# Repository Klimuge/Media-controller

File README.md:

# MediaController

Компактный портативный медиаконтроллер на ESP32-S3 с механическими кнопками и Bluetooth.

## Что это
Устройство подключается к телефону или компьютеру по Bluetooth или type-c кабелю и управляет медиа:
следующий/предыдущий трек, пауза, громкость, выводит название трека, автора, сколько трека прошло,
сколько осталось или сколько он длится. Что выводится на экране и что делает четвёртая кнопка можно настроить

## Железо
- ESP32-S3-WROOM-1-N16R8
- Cherry MX Red — механические кнопки
- EC11 — энкодер для громкости
- LCD 2004 + I2C — дисплей
- LiPo 3.7В 3000мАч аккумулятор
- TP4056 — зарядка
- AP2112K-3.3 — LDO, питание логики 3.3V
- MTS-123 — тумблер переключения режимов

## Что сделано
- Схема и PCB в KiCad
- BOM с футпринтами
- 3д модели корпуса
- План кода

## Программная часть (не реализована)

Система состоит из трёх компонентов.

### Прошивка ESP32

NimBLE-Arduino (h2zero) — устройство представляется системе как BLE HID-клавиатура
и отправляет медиакейкоды. ESP32-S3 работает как составное USB-устройство одновременно:
HID (медиаклавиатура) + CDC (виртуальный COM-порт для агента).
ArduinoJson парсит входящие JSON-сообщения от агента и обновляет LCD.
Тумблер MTS-123 переключает режимы, состояние читается через GPIO38/GPIO39 с INPUT_PULLDOWN.
Энкодер EC11 управляет громкостью через прерывания.

### Агент

Фоновое приложение в системном трее. Читает метаданные текущего трека, системное время и т. д,
отправляет их на устройство по USB Serial (JSON). Если кабель не подключён то по Bluetooth. Также должен запускать программу
если пользователь настроит запуск программы на кастомную (четвёртую) кнопку

### PC-конфигуратор

GUI-приложение (PySide6). Пользователь настраивает устройство через интерфейс,
конфигуратор рендерит Jinja2-шаблон прошивки с этими настройками и автоматически
прошивает устройство через arduino-cli / esptool. Фактически — настройка и перепрошивка
без написания кода.

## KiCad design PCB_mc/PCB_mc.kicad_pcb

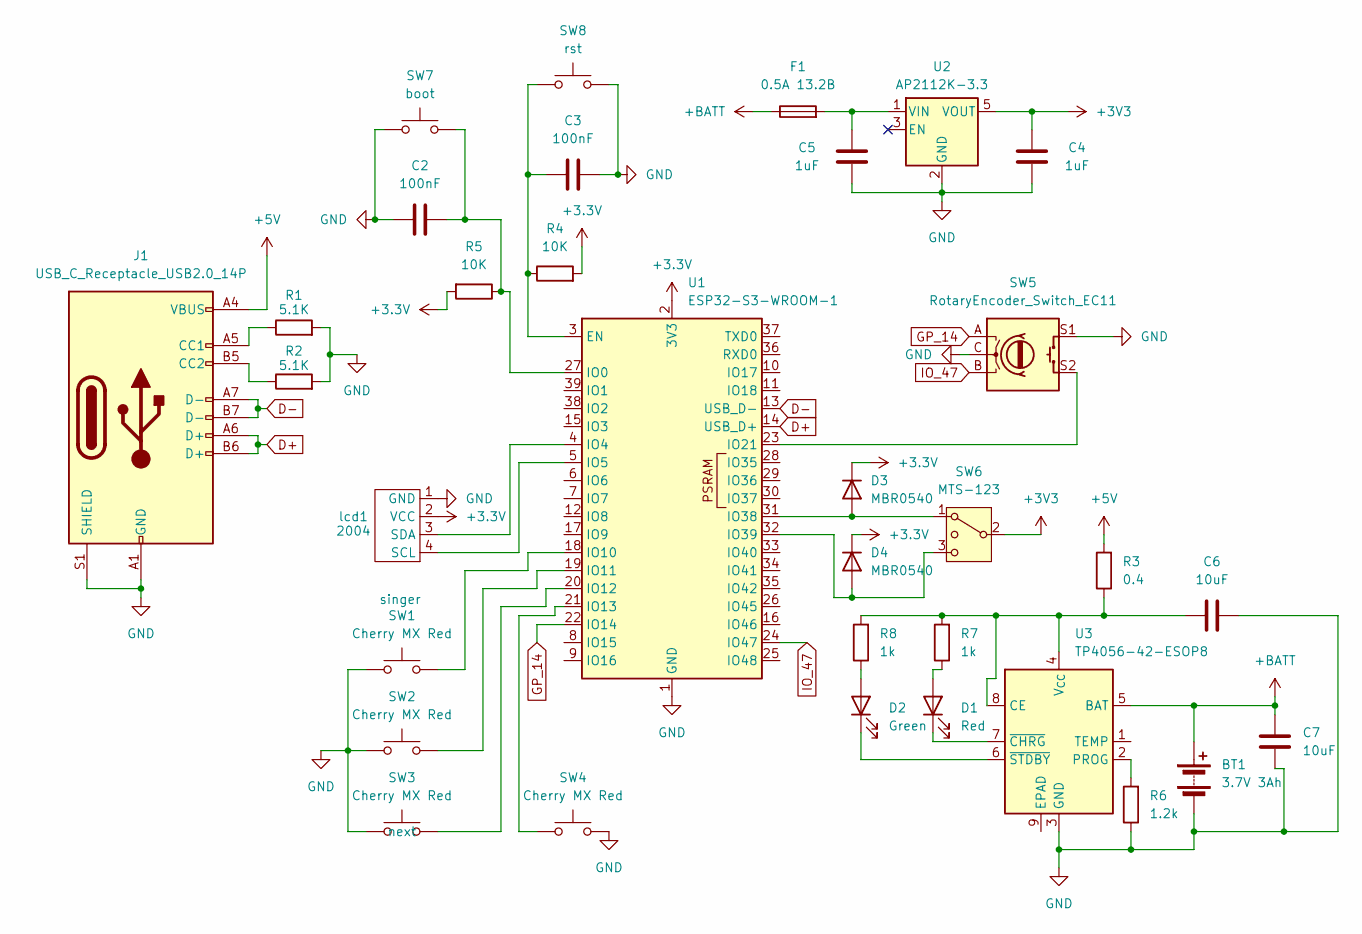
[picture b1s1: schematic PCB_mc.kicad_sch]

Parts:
BT1: 3.7V 3Ah; AMASS_XT60-M_1x02_P7.20mm_Vertical
C2, C3: 100nF; C_1206_3216Metric_Pad1.33x1.80mm_HandSolder
C4, C5: 1uF; C_1206_3216Metric_Pad1.33x1.80mm_HandSolder
C6, C7: 10uF; C_1206_3216Metric_Pad1.33x1.80mm_HandSolder
D1: Red; LED_1206_3216Metric_Pad1.42x1.75mm_HandSolder
D2: Green; LED_1206_3216Metric_Pad1.42x1.75mm_HandSolder
D3, D4: MBR0540; D_SOD-123
F1: 0.5А 13.2В; Fuse_1206_3216Metric_Pad1.42x1.75mm_HandSolder
J1: USB_C_Receptacle_USB2.0_14P; USB_C_Receptacle_GCT_USB4105-xx-A_16P_TopMnt_Horizontal
R1, R2: 5.1K; R_1206_3216Metric_Pad1.30x1.75mm_HandSolder
R3: 0.4; R_1206_3216Metric_Pad1.30x1.75mm_HandSolder
R4, R5: 10К; R_1206_3216Metric_Pad1.30x1.75mm_HandSolder
R6: 1.2k; R_1206_3216Metric_Pad1.30x1.75mm_HandSolder
R7, R8: 1k; R_1206_3216Metric_Pad1.30x1.75mm_HandSolder
SW1, SW2, SW3, SW4: Cherry MX Red; SW_Cherry_MX_1.00u_PCB
SW5: RotaryEncoder_Switch_EC11; RotaryEncoder_Alps_EC11E-Switch_Vertical_H20mm_MountingHoles
SW6: MTS-123; MTS
SW7: boot; SW_PUSH-12mm_Wuerth-430476085716
SW8: rst; SW_PUSH-12mm_Wuerth-430476085716
U1: ESP32-S3-WROOM-1
U2: AP2112K-3.3; SOT-23-5
U3: TP4056-42-ESOP8; SOIC-8-1EP_3.9x4.9mm_P1.27mm_EP2.41x3.3mm_ThermalVias
lcd1: 2004; JST_XH_B4B-XH-A_1x04_P2.50mm_Vertical

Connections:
+3.3V: D3.1 (K), D4.1 (K), R4.2, R5.2, U1.2 (3V3), lcd1.2 (VCC)
+3V3: C4.2, SW6.2 (3), U2.5 (VOUT)
+5V: J1.A4 (VBUS), J1.A9 (VBUS), J1.B4 (VBUS), J1.B9 (VBUS), R3.2
+BATT: BT1.1 (+), C7.1, F1.1, U3.5 (BAT)
D+: J1.A6 (D+), J1.B6 (D+), U1.14 (USB_D+)
D-: J1.A7 (D-), J1.B7 (D-), U1.13 (USB_D-)
GND: BT1.2 (-), C2.1, C3.1, C4.1, C5.1, C6.1, C7.2, J1.A1 (GND), J1.A12 (GND), J1.B1 (GND), J1.B12 (GND), J1.S1 (SHIELD), R1.2, R2.2, R6.1, SW1.1, SW2.1, SW3.1, SW4.2, SW5.C, SW5.S1, SW7.1, SW8.1, U1.1 (GND), U1.40 (GND), U1.41 (GND), U2.2 (GND), U3.3 (GND), lcd1.1 (GND)
GP_14: SW5.A, U1.22 (IO14)
IO_47: SW5.B, U1.24 (IO47)
unnamed: D1.2 (A), R7.1
unnamed: D1.1 (K), U3.7 (~CHRG)
unnamed: D2.2 (A), R8.1
unnamed: D2.1 (K), U3.6 (~STDBY)
unnamed: D3.2 (A), SW6.1, U1.31 (IO38)
unnamed: D4.2 (A), SW6.3 (4), U1.32 (IO39)
unnamed: J1.A5 (CC1), R1.1
unnamed: J1.B5 (CC2), R2.1
unnamed: C3.2, R4.1, SW8.2, U1.3 (EN)
unnamed: C2.2, R5.1, SW7.2, U1.27 (IO0)
unnamed: U1.4 (IO4), lcd1.3 (SDA)
unnamed: U1.5 (IO5), lcd1.4 (SCL)
unnamed: SW1.2, U1.18 (IO10)
unnamed: SW2.2, U1.19 (IO11)
unnamed: SW3.2, U1.20 (IO12)
unnamed: SW4.1, U1.21 (IO13)
unnamed: SW5.S2, U1.23 (IO21)
unnamed: C5.2, F1.2, U2.1 (VIN)
unnamed: C6.2, R3.1, R7.2, R8.2, U3.4 (V_{CC}), U3.8 (CE)
unnamed: R6.2, U3.2 (PROG)

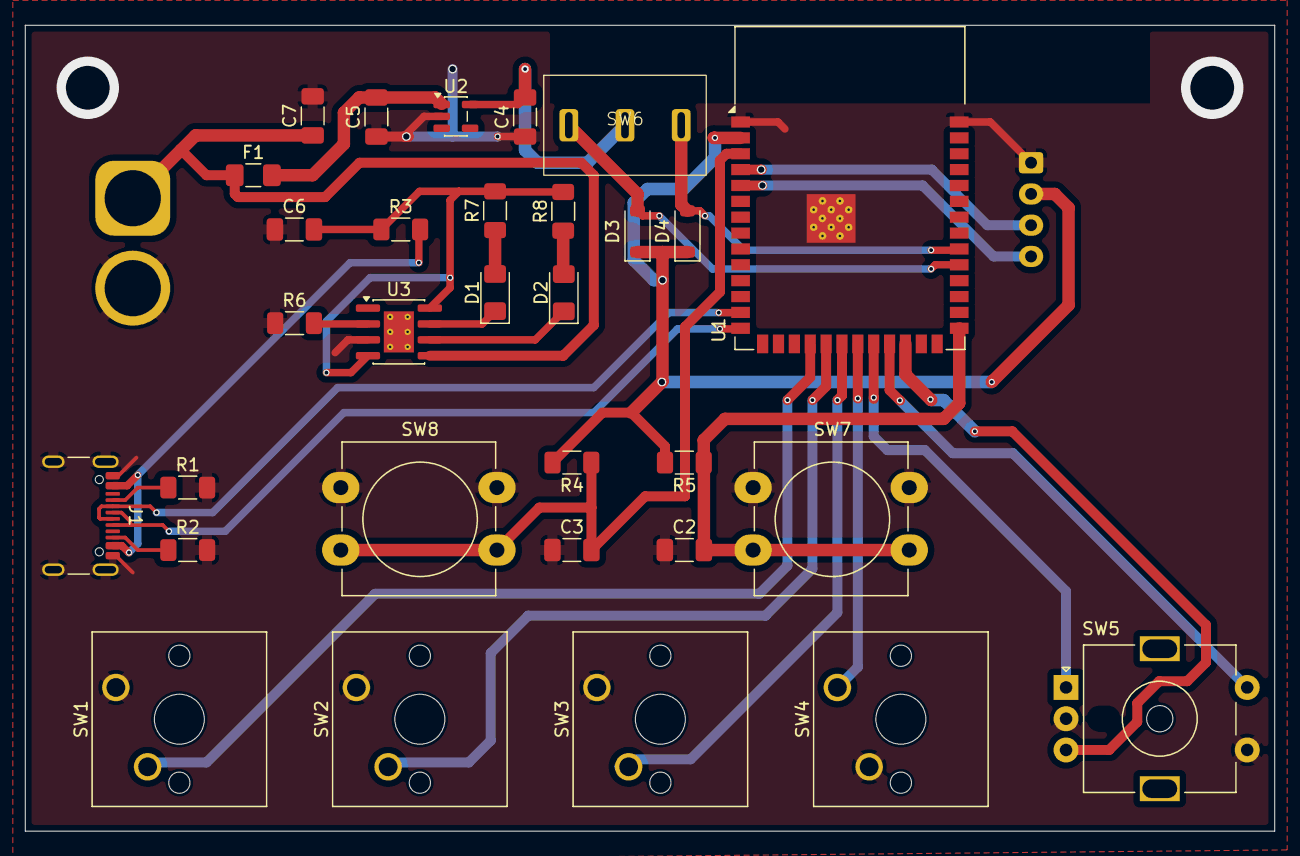
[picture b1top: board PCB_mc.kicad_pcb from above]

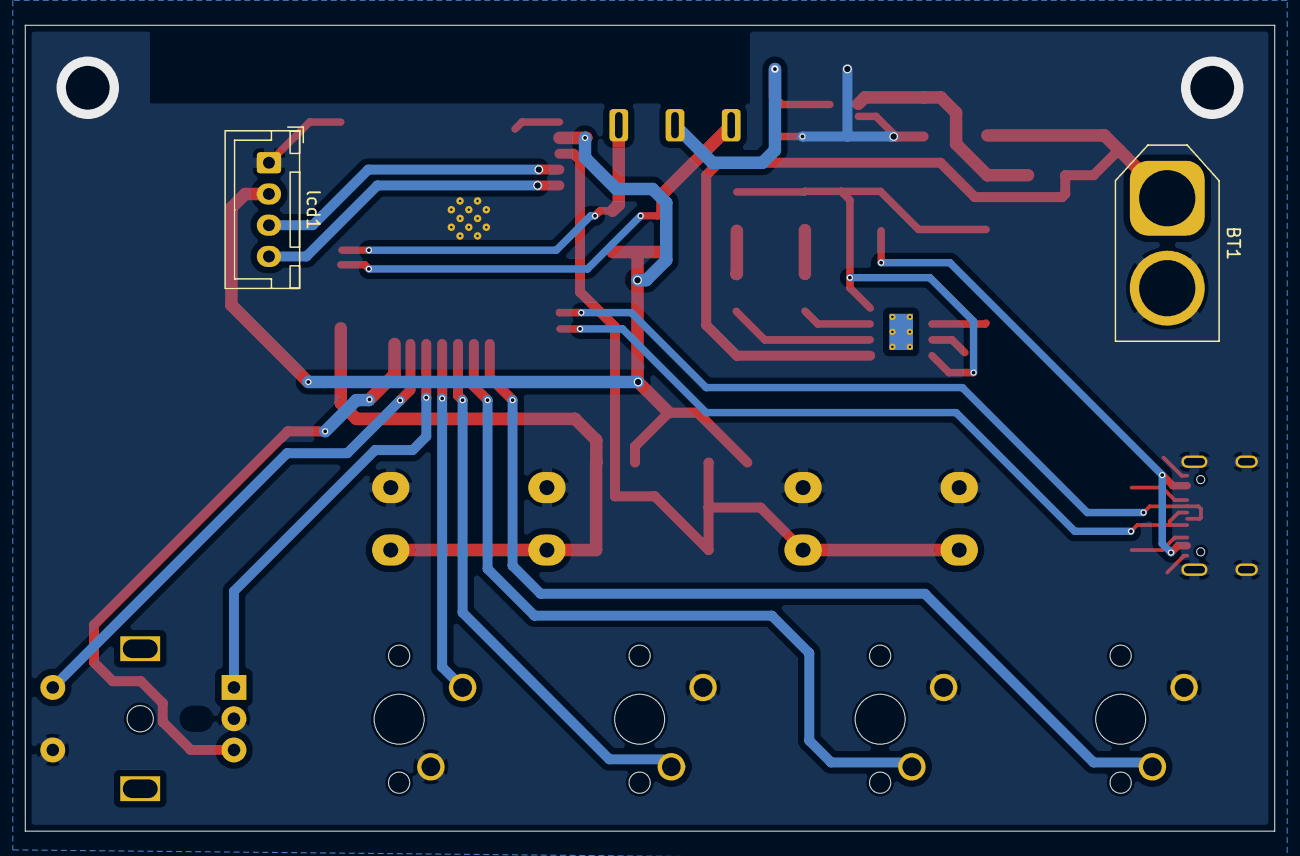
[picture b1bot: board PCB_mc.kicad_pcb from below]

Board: 2 copper layers, 100.0 x 64.5 mm, 33 parts (2 on the bottom side), 29 nets.

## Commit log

2026-05-13 Create a
2026-05-13 Update a
2026-05-14 Исправление README.md
2026-05-14 Udalil Herhu
2026-05-14 Obnova README.md
